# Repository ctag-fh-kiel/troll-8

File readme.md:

# CTAG TROLL8
TROLL8 is an Arduino Based μSynth development platform.
This repo contains:
  - [KiCad](http://kicad.org/) PCB design files ([schematics as pdf](https://github.com/ctag-fh-kiel/troll-8/blob/master/Docs/TROLL-8-Schematics.pdf))
	- You may order the PCB [here](http://dirtypcbs.com/store/designer/details/8229/2509/gerber-zip)
  - Silkscreen design files
  - Arduino examples
    - Midi controller (requires [hairless midi](http://projectgus.github.io/hairless-midiserial/))
	- Drum machine with Synth
    - ePiano (velocity sensitive)    
	- Step sequencer
    - Linear sequencer
    - Teensy 3.1 synthesizer
    - LED example
    - and more...
  - A short [presentation on TROLL8](https://github.com/ctag-fh-kiel/troll-8/blob/master/Docs/Talk_AmIEs2016_Manzke.pdf)
# Known Bugs
  - PCB design: Rotary knobs are not evenly spaced
# Authors / License
  - Authors are Robert Manzke (Main Author, FH-Kiel), Henrik Langer (FH-Kiel), Alexander Konradi (FH-Kiel)
  - Licensed under Creative Commons Attribution-NonCommercial-ShareAlike 4.0 International License
# Acknoledgements
  - All Arduino examples make use of the amazing [Mozzi Sound Library](http://sensorium.github.io/Mozzi/)
# Media

## [Gearnews English (click here)](https://www.gearnews.com/troll8-micro-sized-synthesizer-sequencer-controller-drum-machine/)

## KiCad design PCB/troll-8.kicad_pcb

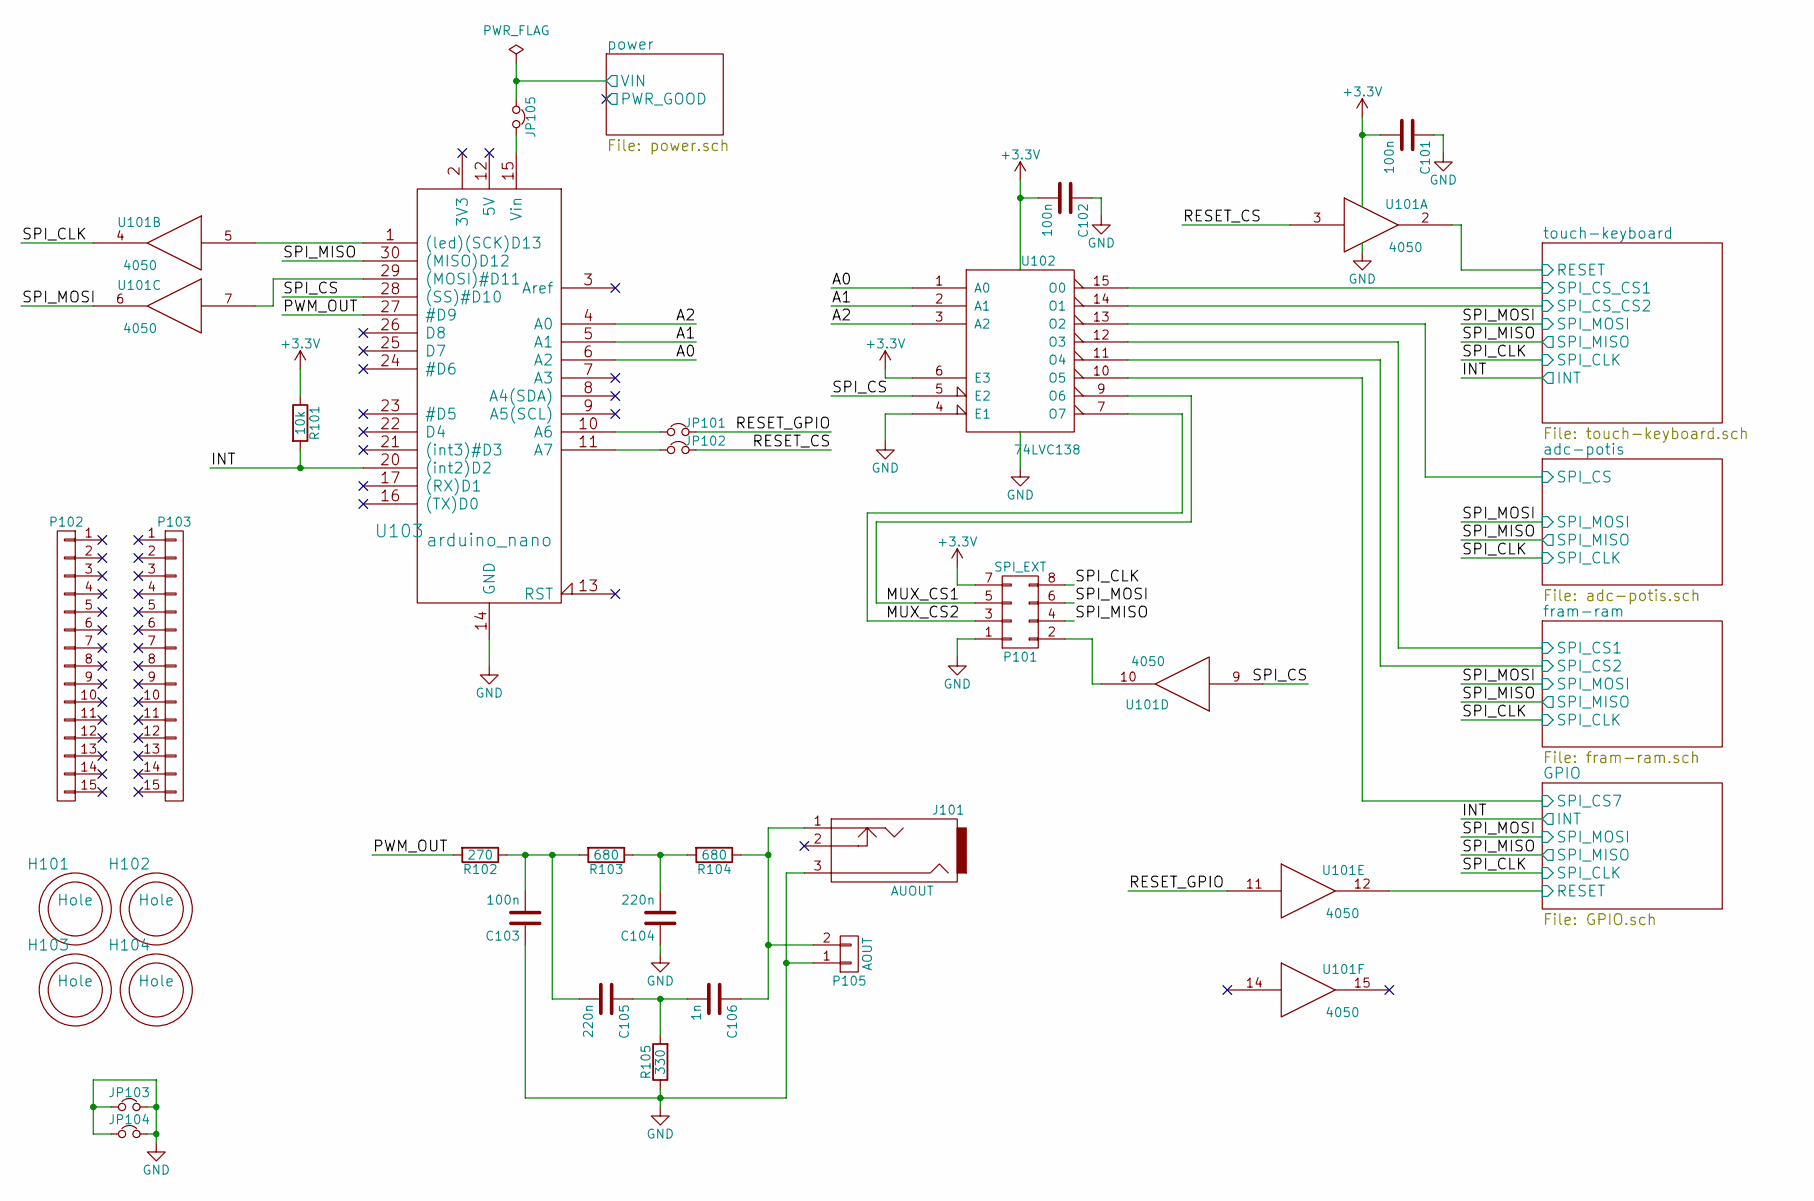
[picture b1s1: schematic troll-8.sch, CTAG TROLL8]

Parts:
C101, C102, C103: 100n; C_0603_HandSoldering
C104, C105: 220n; C_0603_HandSoldering
C106: 1n; C_0603_HandSoldering
H101, H102, H103, H104: Hole; Hole_3mm
J101: AUOUT; THONKICONN
JP101, JP102: Jumper_NC_Small; R_0603_HandSoldering
JP103, JP104: Jumper_NC_Small; R_0805_HandSoldering
JP105: Jumper_NC_Small; Pin_Header_Straight_1x02
P101: SPI_EXT; Pin_Header_Straight_2x04
P102, P103: Pin_Header_Straight_1x15
P105: AOUT; Pin_Header_Straight_1x02
R101: 10k; R_0603_HandSoldering
R102: 270; R_0603_HandSoldering
R103, R104: 680; R_0603_HandSoldering
R105: 330; R_0603_HandSoldering
U101: 4050; TSSOP-16_4.4x5mm_Pitch0.65mm
U102: 74LVC138; TSSOP-16_4.4x5mm_Pitch0.65mm
U103: arduino_nano; arduino_mini

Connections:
+3V3: C101.2, C102.2, P101.7, R101.1, U101.1 (VCC), U102.6 (E3), U102.16 (VCC); also elsewhere on the board
/A0: U102.1 (A0), U103.6 (A2)
/A1: U102.2 (A1), U103.5 (A1)
/A2: U102.3 (A2), U103.4 (A0)
/GPIO/RESET: U101.12; also elsewhere on the board
/GPIO/SPI_CS7: U102.10 (O5); also elsewhere on the board
/INT: R101.2, U103.20 ((int2)D2); also elsewhere on the board
/MUX_CS1: P101.5, U102.9 (O6)
/MUX_CS2: P101.3, U102.7 (O7)
/PWM_OUT: R102.2, U103.27 (#D9)
/RESET_CS: JP102.2, U101.3
/RESET_GPIO: JP101.2, U101.11
/SPI_CLK: P101.8, U101.4; also elsewhere on the board
/SPI_CS: U101.9, U102.5 (E2), U103.28 ((SS)#D10)
/SPI_MISO: P101.4, U103.30 ((MISO)D12); also elsewhere on the board
/SPI_MOSI: P101.6, U101.6; also elsewhere on the board
/adc-potis/SPI_CS: U102.13 (O2); also elsewhere on the board
/fram-ram/SPI_CS1: U102.12 (O3); also elsewhere on the board
/fram-ram/SPI_CS2: U102.11 (O4); also elsewhere on the board
/power/VIN: JP105.1; also elsewhere on the board
/touch-keyboard/RESET: U101.2; also elsewhere on the board
/touch-keyboard/SPI_CS_CS1: U102.15 (O0); also elsewhere on the board
/touch-keyboard/SPI_CS_CS2: U102.14 (O1); also elsewhere on the board
GND: C101.1, C102.1, C103.1, C104.1, J101.3, JP103.1, JP103.2, JP104.1, JP104.2, P101.1, P105.1, R105.1, U101.8 (VSS), U102.4 (E1), U102.8 (GND), U103.14 (GND), U103.19 (GND); also elsewhere on the board
unnamed: C103.2, C105.2, R102.1, R103.2
unnamed: C104.2, R103.1, R104.2
unnamed: C105.1, C106.2, R105.2
unnamed: C106.1, J101.1, P105.2, R104.1
unnamed: JP101.1, U103.10 (A6)
unnamed: JP102.1, U103.11 (A7)
unnamed: JP105.2, U103.15 (Vin)
unnamed: P101.2, U101.10
unnamed: U101.5, U103.1 ((led)(SCK)D13)
unnamed: U101.7, U103.29 ((MOSI)#D11)

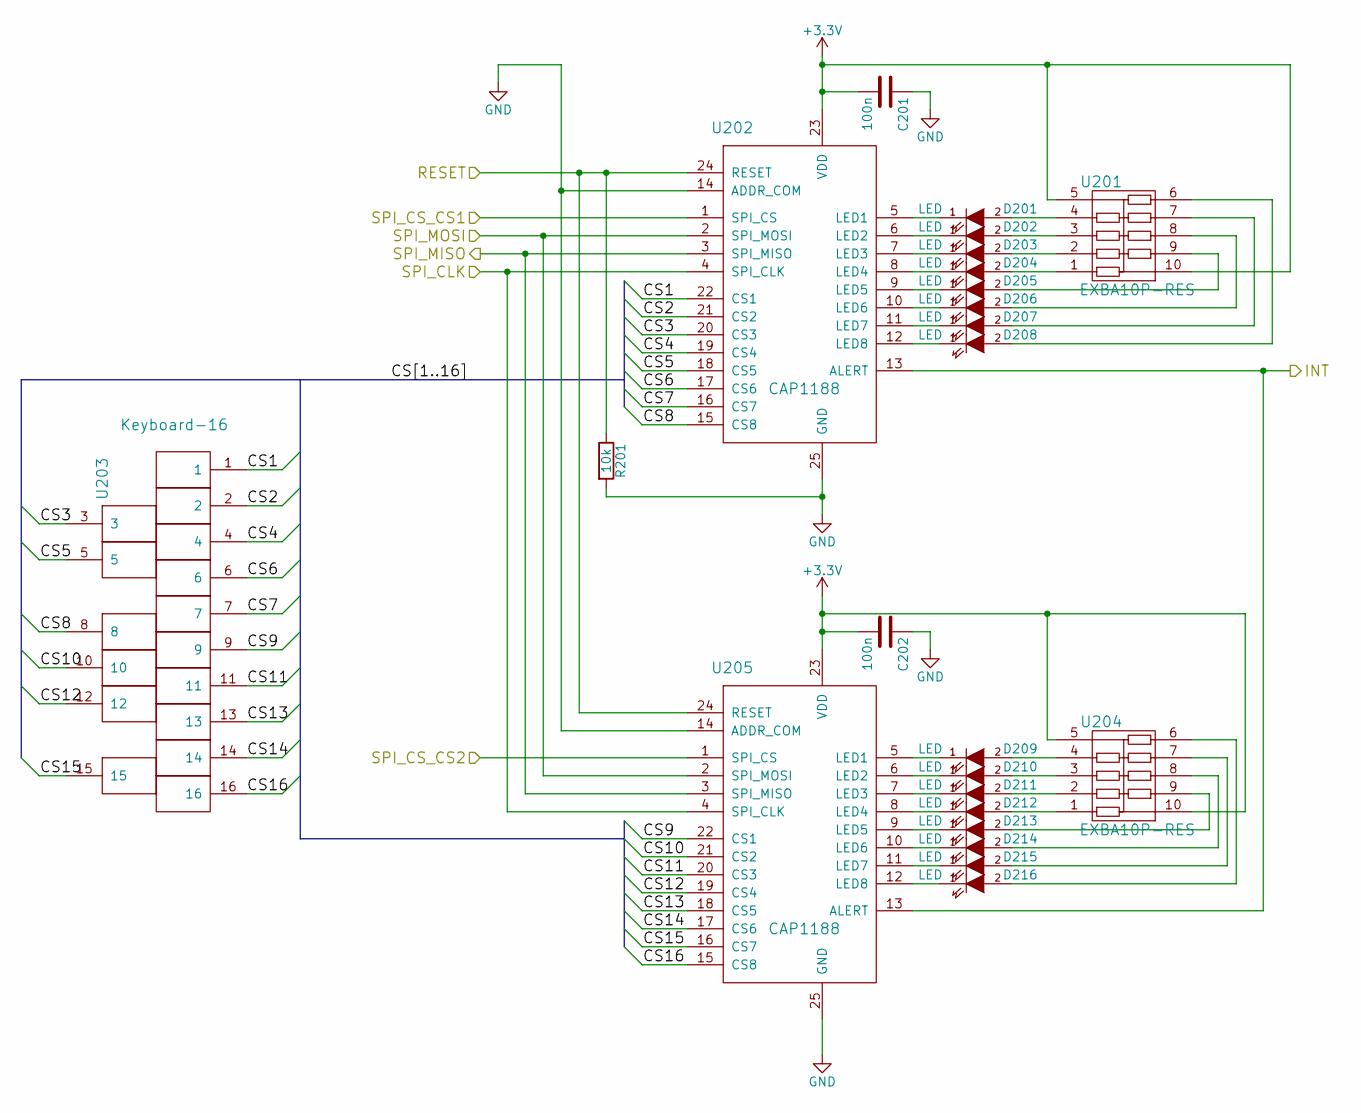
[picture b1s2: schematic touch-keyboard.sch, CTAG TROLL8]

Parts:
C201, C202: 100n; C_0603_HandSoldering
D201, D202, D203, D204, D205, D206, D207, D208, D209, D210, D211, D212, D213, D214, D215, D216: LED; LED-0603
R201: 10k; R_0603_HandSoldering
U201, U204: EXBA10P-RES; EXBA10P
U202, U205: CAP1188; QFN-24-1EP_4x4mm_Pitch0.5mm
U203: Keyboard-16; midi-keyboard-16

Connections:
+3V3: C201.2, C202.2, U201.5, U201.10, U202.23 (VDD), U204.5, U204.10, U205.23 (VDD); also elsewhere on the board
/INT: U202.13 (ALERT), U205.13 (ALERT); also elsewhere on the board
/SPI_CLK: U202.4 (SPI_CLK), U205.4 (SPI_CLK); also elsewhere on the board
/SPI_MISO: U202.3 (SPI_MISO), U205.3 (SPI_MISO); also elsewhere on the board
/SPI_MOSI: U202.2 (SPI_MOSI), U205.2 (SPI_MOSI); also elsewhere on the board
/touch-keyboard/CS1: U202.22 (CS1), U203.1
/touch-keyboard/CS2: U202.21 (CS2), U203.2
/touch-keyboard/CS3: U202.20 (CS3), U203.3
/touch-keyboard/CS4: U202.19 (CS4), U203.4
/touch-keyboard/CS5: U202.18 (CS5), U203.5
/touch-keyboard/CS6: U202.17 (CS6), U203.6
/touch-keyboard/CS7: U202.16 (CS7), U203.7
/touch-keyboard/CS8: U202.15 (CS8), U203.8
/touch-keyboard/CS9: U203.9, U205.22 (CS1)
/touch-keyboard/CS10: U203.10, U205.21 (CS2)
/touch-keyboard/CS11: U203.11, U205.20 (CS3)
/touch-keyboard/CS12: U203.12, U205.19 (CS4)
/touch-keyboard/CS13: U203.13, U205.18 (CS5)
/touch-keyboard/CS14: U203.14, U205.17 (CS6)
/touch-keyboard/CS15: U203.15, U205.16 (CS7)
/touch-keyboard/CS16: U203.16, U205.15 (CS8)
/touch-keyboard/RESET: R201.1, U202.24 (RESET), U205.24 (RESET); also elsewhere on the board
/touch-keyboard/SPI_CS_CS1: U202.1 (SPI_CS); also elsewhere on the board
/touch-keyboard/SPI_CS_CS2: U205.1 (SPI_CS); also elsewhere on the board
GND: C201.1, C202.1, R201.2, U202.14 (ADDR_COM), U202.25 (GND), U205.14 (ADDR_COM), U205.25 (GND); also elsewhere on the board
unnamed: D201.1 (K), U202.5 (LED1)
unnamed: D201.2 (A), U201.4
unnamed: D202.1 (K), U202.6 (LED2)
unnamed: D202.2 (A), U201.3
unnamed: D203.1 (K), U202.7 (LED3)
unnamed: D203.2 (A), U201.2
unnamed: D204.1 (K), U202.8 (LED4)
unnamed: D204.2 (A), U201.1
unnamed: D205.1 (K), U202.9 (LED5)
unnamed: D205.2 (A), U201.9
unnamed: D206.1 (K), U202.10 (LED6)
unnamed: D206.2 (A), U201.8
unnamed: D207.1 (K), U202.11 (LED7)
unnamed: D207.2 (A), U201.7
unnamed: D208.1 (K), U202.12 (LED8)
unnamed: D208.2 (A), U201.6
unnamed: D209.1 (K), U205.5 (LED1)
unnamed: D209.2 (A), U204.4
unnamed: D210.1 (K), U205.6 (LED2)
unnamed: D210.2 (A), U204.3
unnamed: D211.1 (K), U205.7 (LED3)
unnamed: D211.2 (A), U204.2
unnamed: D212.1 (K), U205.8 (LED4)
unnamed: D212.2 (A), U204.1
unnamed: D213.1 (K), U205.9 (LED5)
unnamed: D213.2 (A), U204.9
unnamed: D214.1 (K), U205.10 (LED6)
unnamed: D214.2 (A), U204.8
unnamed: D215.1 (K), U205.11 (LED7)
unnamed: D215.2 (A), U204.7
unnamed: D216.1 (K), U205.12 (LED8)
unnamed: D216.2 (A), U204.6

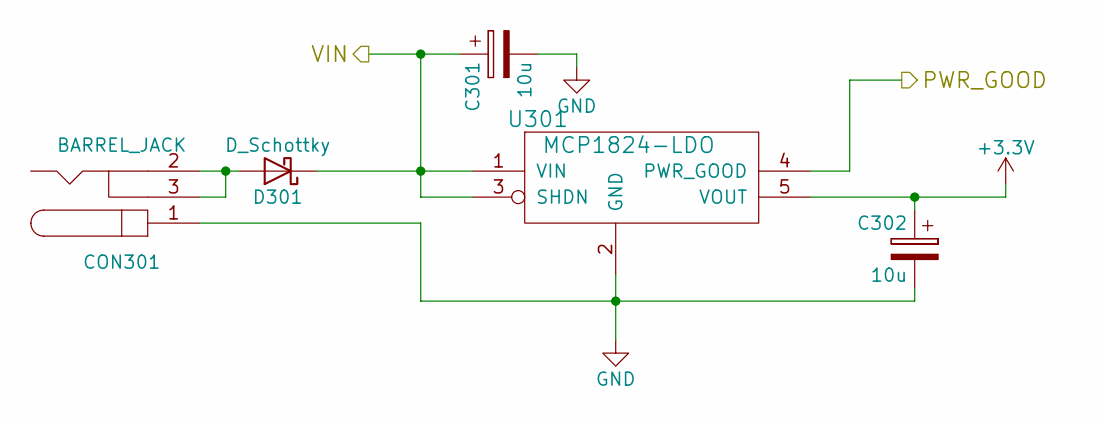
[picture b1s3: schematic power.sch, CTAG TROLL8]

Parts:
C301, C302: 10u; c_elec_4x5.7
CON301: BARREL_JACK; BARELL_CLIFF_DC10L
D301: D_Schottky; SOD-123
U301: MCP1824-LDO; SOT-23-5

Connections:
+3V3: C302.1, U301.5 (VOUT); also elsewhere on the board
/power/PWR_GOOD: U301.4 (PWR_GOOD)
/power/VIN: C301.1, D301.1 (K), U301.1 (VIN), U301.3 (SHDN); also elsewhere on the board
GND: C301.2, C302.2, CON301.1, U301.2 (GND); also elsewhere on the board
unnamed: CON301.2, CON301.3, D301.2 (A)

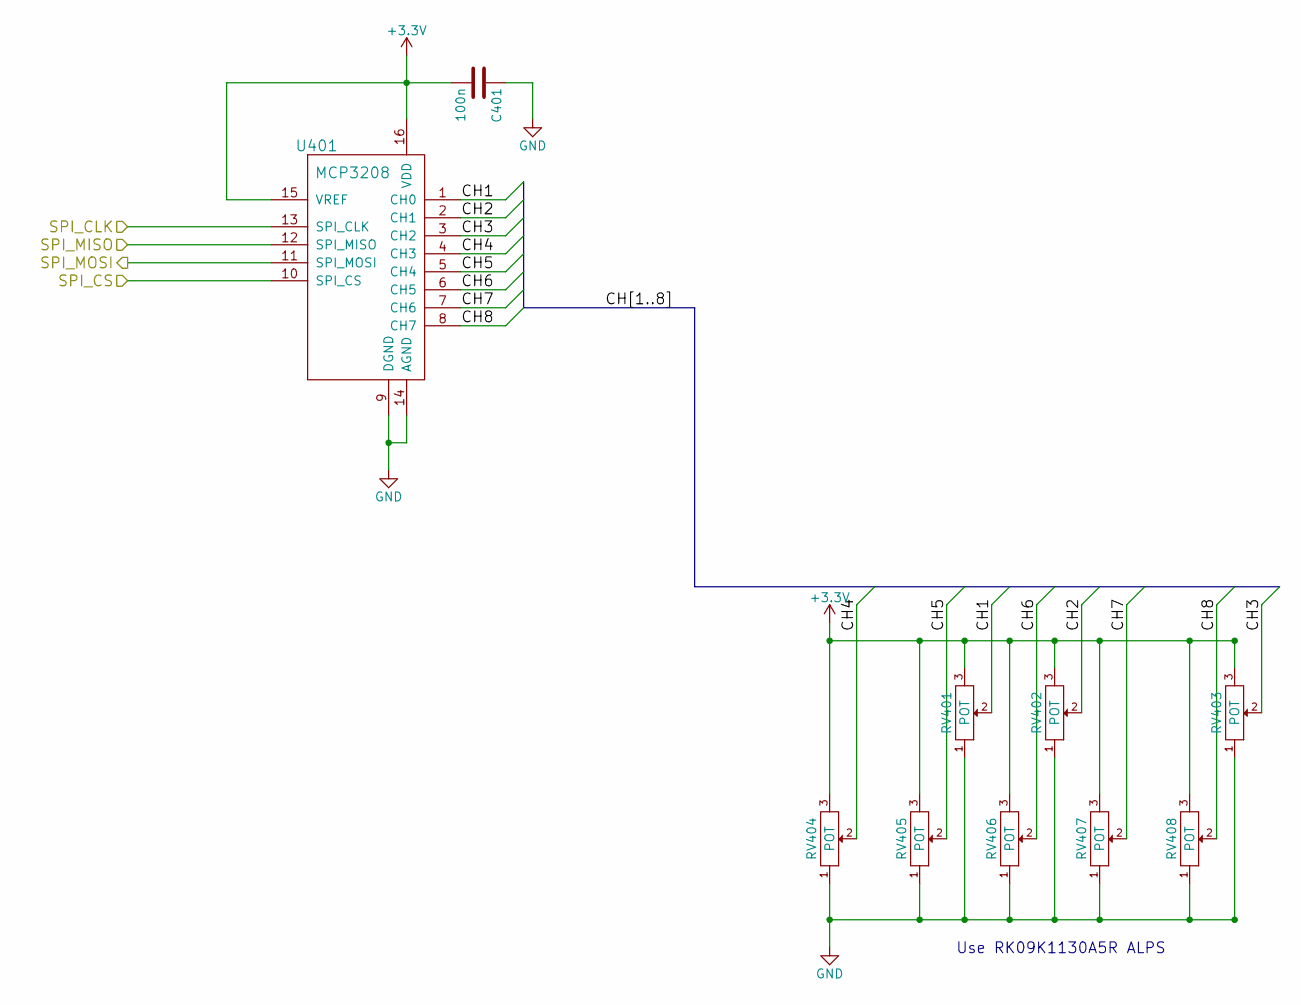
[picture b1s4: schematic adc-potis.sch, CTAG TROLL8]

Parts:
C401: 100n; C_0603_HandSoldering
RV401, RV402, RV403, RV404, RV405, RV406, RV407, RV408: POT; Alps-RK09
U401: MCP3208; SOIC-16_3.9x9.9mm_Pitch1.27mm

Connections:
+3V3: C401.2, RV401.3, RV402.3, RV403.3, RV404.3, RV405.3, RV406.3, RV407.3, RV408.3, U401.15 (VREF), U401.16 (VDD); also elsewhere on the board
/SPI_CLK: U401.13 (SPI_CLK); also elsewhere on the board
/SPI_MISO: U401.12 (SPI_MISO); also elsewhere on the board
/SPI_MOSI: U401.11 (SPI_MOSI); also elsewhere on the board
/adc-potis/CH1: RV401.2, U401.1 (CH0)
/adc-potis/CH2: RV402.2, U401.2 (CH1)
/adc-potis/CH3: RV403.2, U401.3 (CH2)
/adc-potis/CH4: RV404.2, U401.4 (CH3)
/adc-potis/CH5: RV405.2, U401.5 (CH4)
/adc-potis/CH6: RV406.2, U401.6 (CH5)
/adc-potis/CH7: RV407.2, U401.7 (CH6)
/adc-potis/CH8: RV408.2, U401.8 (CH7)
/adc-potis/SPI_CS: U401.10 (SPI_CS); also elsewhere on the board
GND: C401.1, RV401.1, RV402.1, RV403.1, RV404.1, RV405.1, RV406.1, RV407.1, RV408.1, U401.9 (DGND), U401.14 (AGND); also elsewhere on the board

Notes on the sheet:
Use RK09K1130A5R ALPS

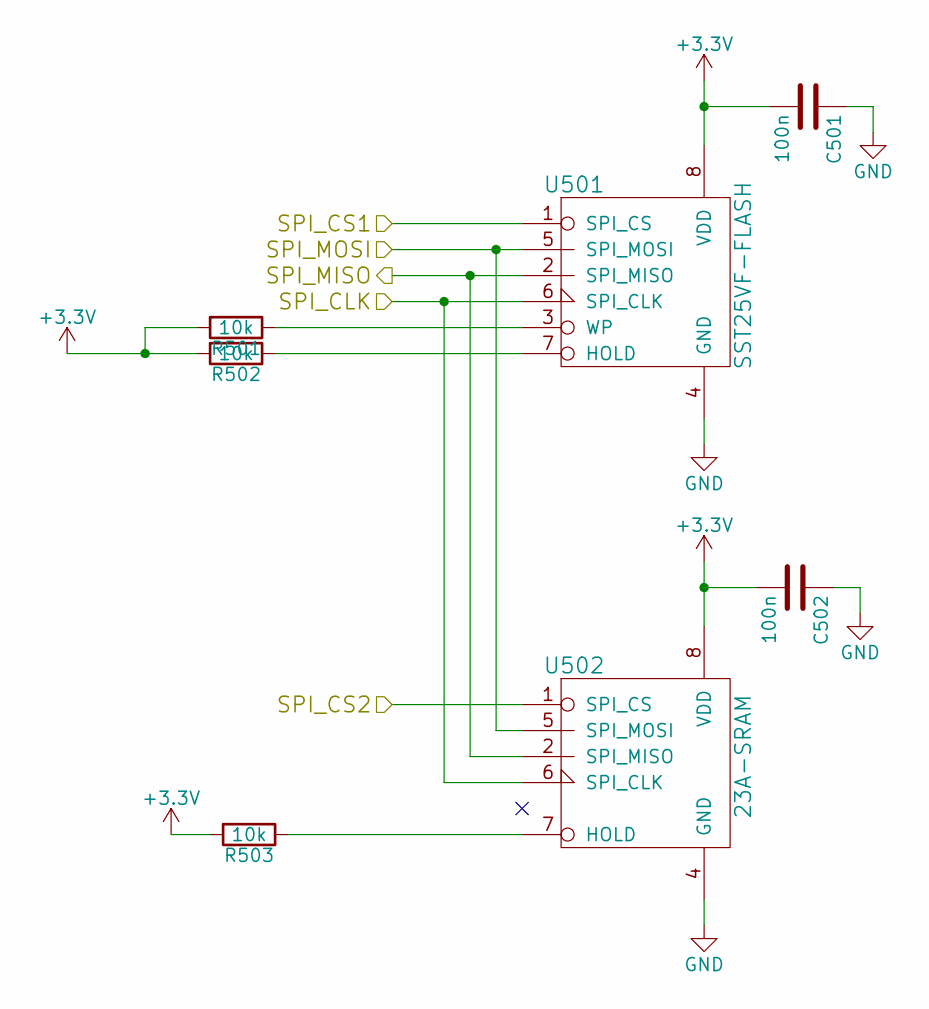
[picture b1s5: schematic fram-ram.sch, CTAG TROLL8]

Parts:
C501, C502: 100n; C_0603_HandSoldering
R501, R502, R503: 10k; R_0603_HandSoldering
U501: SST25VF-FLASH; SOIC-8_3.9x4.9mm_Pitch1.27mm
U502: 23A-SRAM; SOIC-8_3.9x4.9mm_Pitch1.27mm

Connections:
+3V3: C501.2, C502.2, R501.2, R502.2, R503.2, U501.8 (VDD), U502.8 (VDD); also elsewhere on the board
/SPI_CLK: U501.6 (SPI_CLK), U502.6 (SPI_CLK); also elsewhere on the board
/SPI_MISO: U501.2 (SPI_MISO), U502.2 (SPI_MISO); also elsewhere on the board
/SPI_MOSI: U501.5 (SPI_MOSI), U502.5 (SPI_MOSI); also elsewhere on the board
/fram-ram/SPI_CS1: U501.1 (SPI_CS); also elsewhere on the board
/fram-ram/SPI_CS2: U502.1 (SPI_CS); also elsewhere on the board
GND: C501.1, C502.1, U501.4 (GND), U502.4 (GND); also elsewhere on the board
unnamed: R501.1, U501.3 (WP)
unnamed: R502.1, U501.7 (HOLD)
unnamed: R503.1, U502.7 (HOLD)

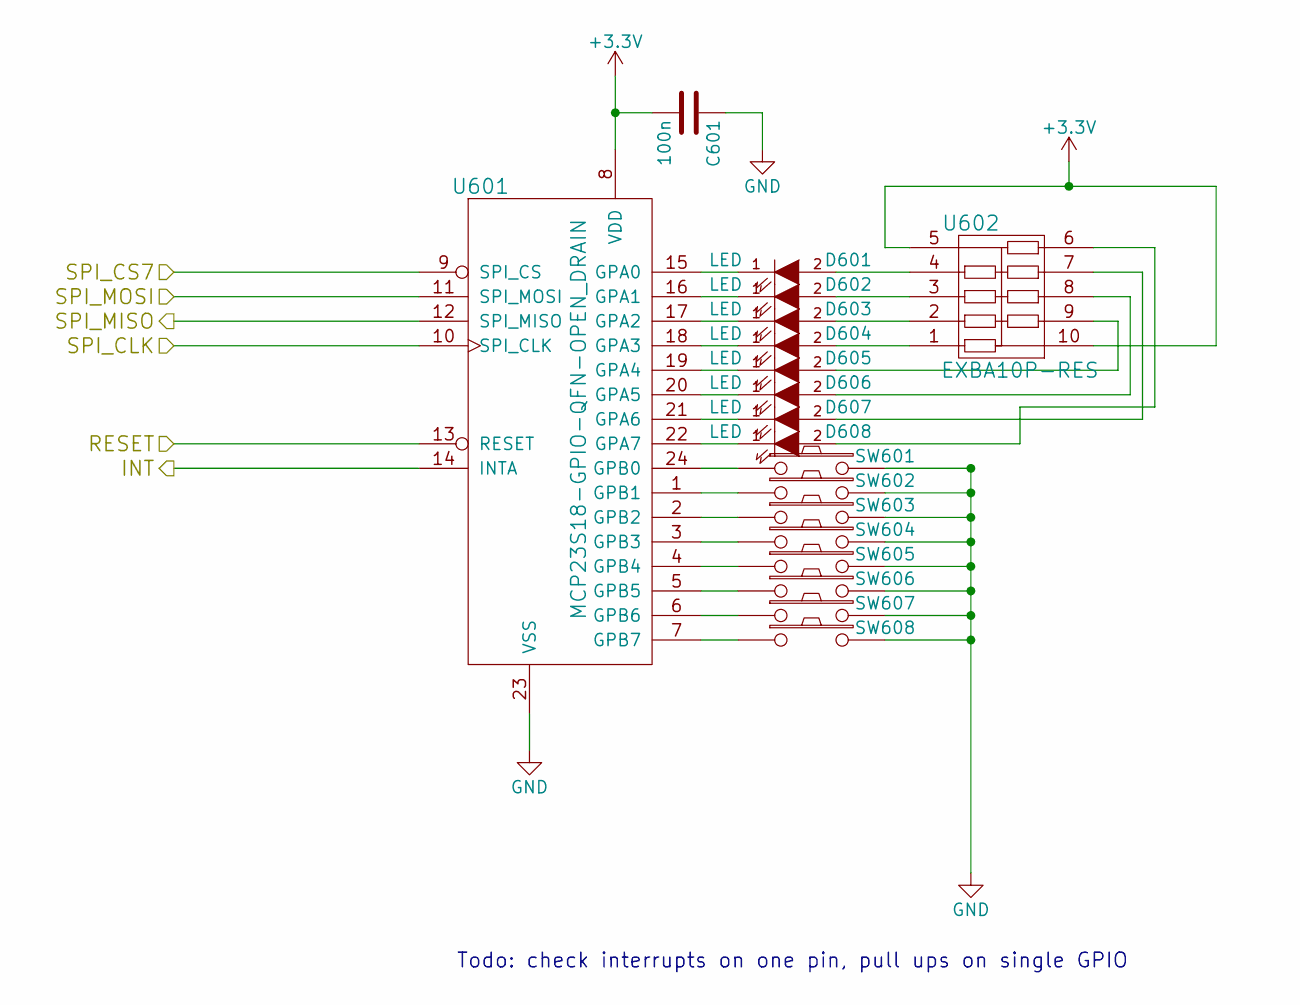
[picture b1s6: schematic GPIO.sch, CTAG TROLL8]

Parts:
C601: 100n; C_0603_HandSoldering
D601, D602, D603, D604, D605, D606, D607, D608: LED; LED-0603
SW601, SW602, SW603, SW604, SW605, SW606, SW607, SW608: SW_PUSH; TE-147873-1-Pushbutton
U601: MCP23S18-GPIO-QFN-OPEN_DRAIN; QFN-24-1EP_4x4mm_Pitch0.5mm
U602: EXBA10P-RES; EXBA10P

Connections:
+3V3: C601.2, U601.8 (VDD), U602.5, U602.10; also elsewhere on the board
/GPIO/RESET: U601.13 (RESET); also elsewhere on the board
/GPIO/SPI_CS7: U601.9 (SPI_CS); also elsewhere on the board
/INT: U601.14 (INTA); also elsewhere on the board
/SPI_CLK: U601.10 (SPI_CLK); also elsewhere on the board
/SPI_MISO: U601.12 (SPI_MISO); also elsewhere on the board
/SPI_MOSI: U601.11 (SPI_MOSI); also elsewhere on the board
GND: C601.1, SW601.2, SW602.2, SW603.2, SW604.2, SW605.2, SW606.2, SW607.2, SW608.2, U601.23 (VSS); also elsewhere on the board
unnamed: D601.1 (K), U601.15 (GPA0)
unnamed: D601.2 (A), U602.4
unnamed: D602.1 (K), U601.16 (GPA1)
unnamed: D602.2 (A), U602.3
unnamed: D603.1 (K), U601.17 (GPA2)
unnamed: D603.2 (A), U602.2
unnamed: D604.1 (K), U601.18 (GPA3)
unnamed: D604.2 (A), U602.1
unnamed: D605.1 (K), U601.19 (GPA4)
unnamed: D605.2 (A), U602.9
unnamed: D606.1 (K), U601.20 (GPA5)
unnamed: D606.2 (A), U602.8
unnamed: D607.1 (K), U601.21 (GPA6)
unnamed: D607.2 (A), U602.7
unnamed: D608.1 (K), U601.22 (GPA7)
unnamed: D608.2 (A), U602.6
unnamed: SW601.1, U601.24 (GPB0)
unnamed: SW602.1, U601.1 (GPB1)
unnamed: SW603.1, U601.2 (GPB2)
unnamed: SW604.1, U601.3 (GPB3)
unnamed: SW605.1, U601.4 (GPB4)
unnamed: SW606.1, U601.5 (GPB5)
unnamed: SW607.1, U601.6 (GPB6)
unnamed: SW608.1, U601.7 (GPB7)

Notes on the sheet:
Todo: check interrupts on one pin, pull ups on single GPIO

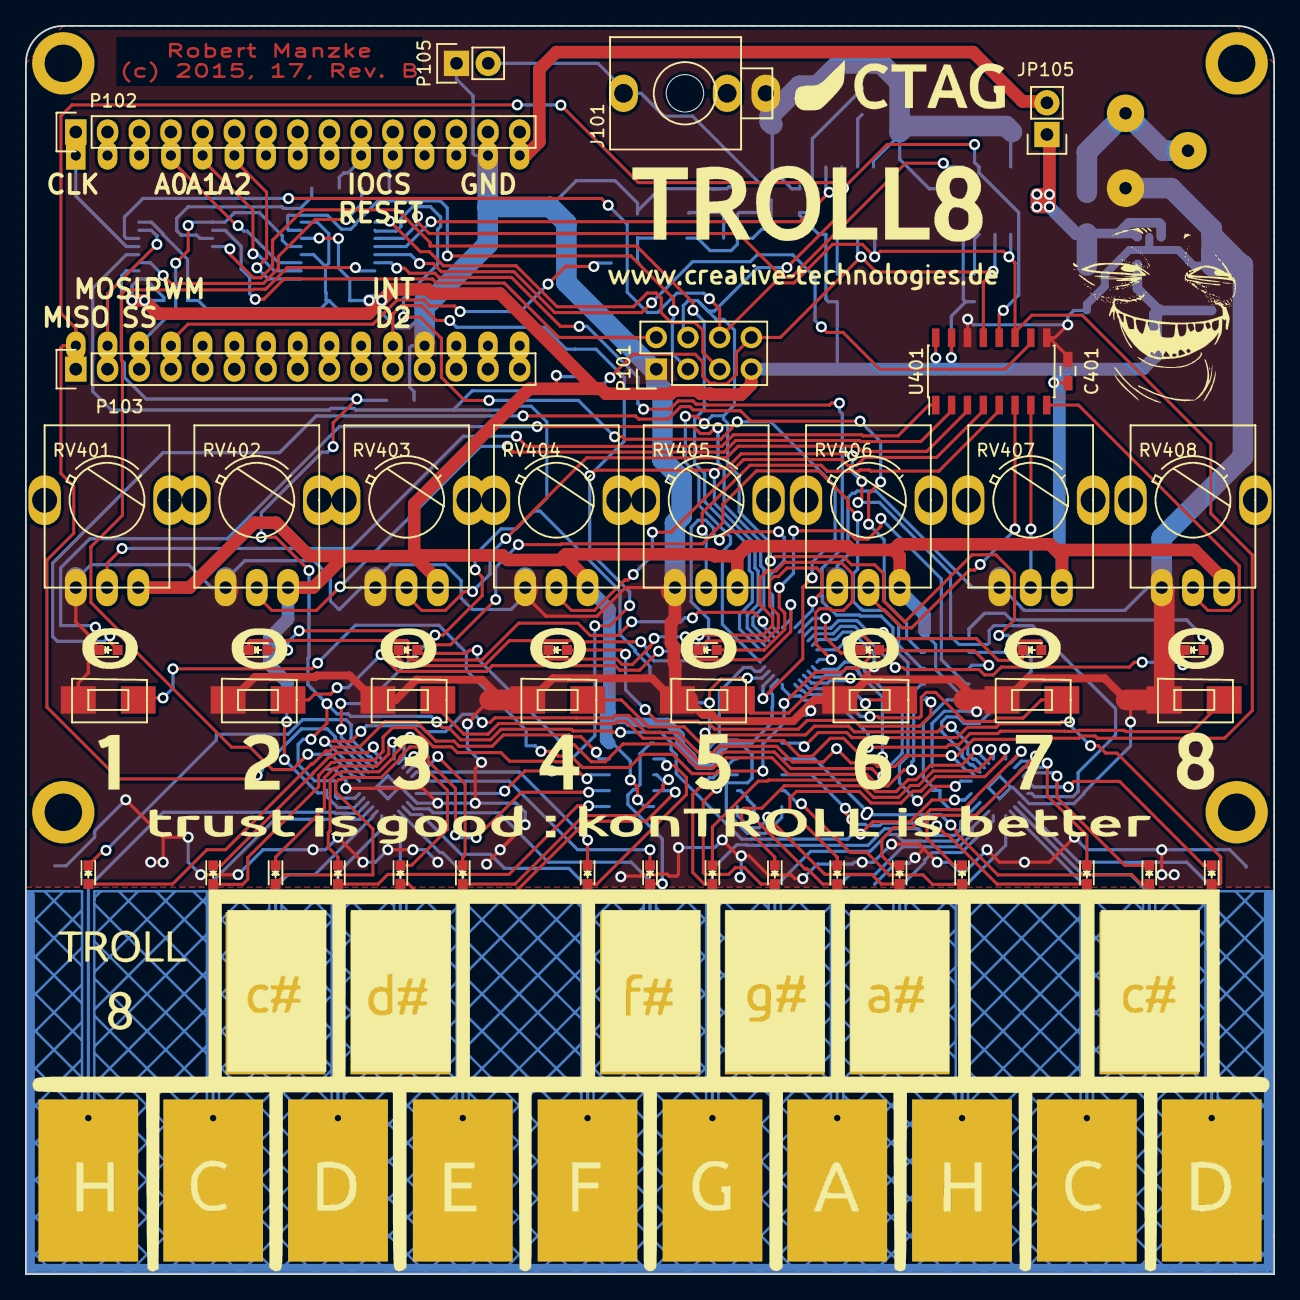
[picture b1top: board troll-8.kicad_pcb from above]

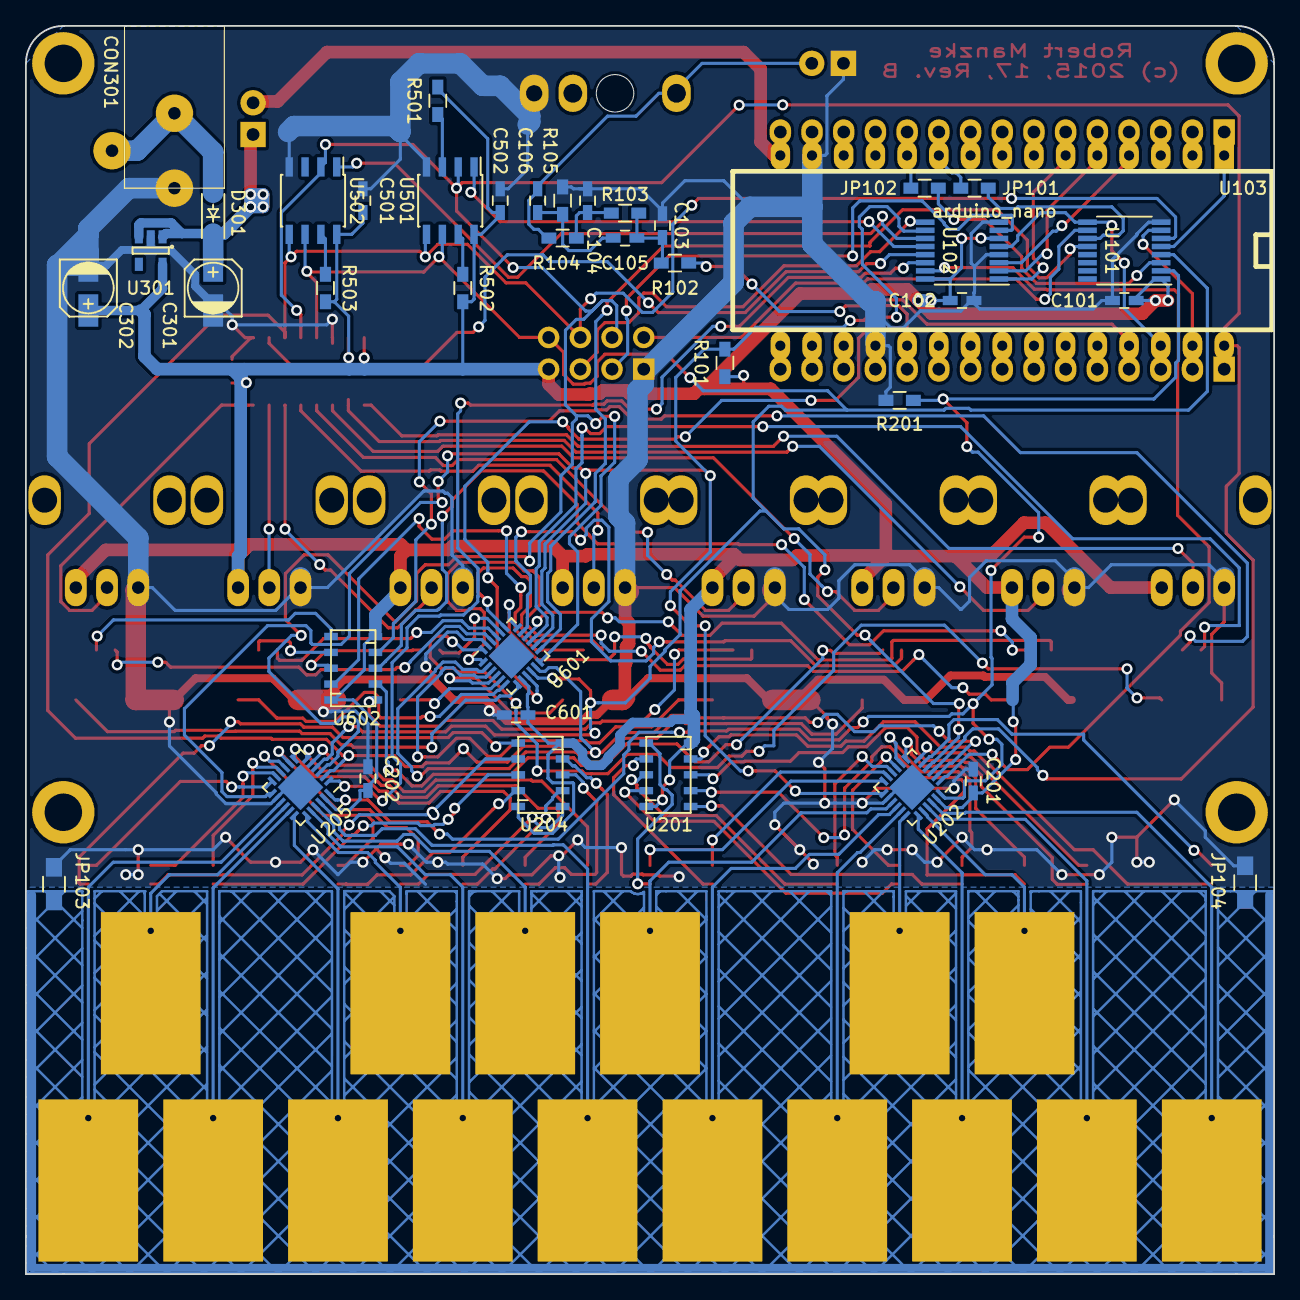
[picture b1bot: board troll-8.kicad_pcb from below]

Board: 2 copper layers, 100.0 x 100.0 mm, 93 parts (40 on the bottom side), 118 nets.

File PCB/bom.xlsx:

Mouser | Id | Designator | Package | Quantity | Designation | Manuf ID |  | Notes
x | 1 | C103,C102,C101,C201,C202,C401,C502,C501,C601 | C_0603_HandSoldering | 9 | 100n | C0603C104K5RACTU
x | 2 | C104, C105 | C_0603_HandSoldering | 2 | 220n | 02016D224KAT2A
x | 3 | C106 | C_0603_HandSoldering | 1 | 1n | GCM188R71H102KA37D
x | 4 | C301,C302 | c_elec_4x5.7 | 2 | 10u | EEE-FC1C100R
x | 5 | CON301 | BARELL_CLIFF_DC10L | 1 | BARREL_JACK | PJ-102B
x | 6 | D201,D202,D203,D204,D205,D206,D207,D208,D209,D210,D211,D212,D213,D214,D215,D216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 | LED-0603 | 24 | LED | 696-SMLLXFP0603SICTR
x | 7 | D301 | SOD-123 | 1 | D_Schottky | STPS140Z
x | 8 | JP101,JP102 | R_0603_HandSoldering | 2 | Jumper_NC_Small | ERJ-3GEY0R00V
Thonk | 9 | J101 | Thonkicon | 1 | AUOUT | PJ301M-12 |  | https://www.thonk.co.uk/shop/3-5mm-jacks/
x | 10 | R102 | R_0603_HandSoldering | 1 | 270 | ERJ3EKF2700V
x | 11 | R103,R104 | R_0603_HandSoldering | 2 | 680 | ERJ3EKF6800V
x | 12 | R105 | R_0603_HandSoldering | 1 | 330 | ERJ3EKF3300V
x | 13 | R201,R501,R502,R503,R101 | R_0603_HandSoldering | 5 | 10k | ERJ3EKF1002V
x | 14 | SW601,SW602,SW603,SW604,SW605,SW606,SW607,SW608 | TE-147873-1-Pushbutton | 8 | SW_PUSH | 147873-1
x | 15 | U102 | TSSOP-16_4.4x5mm_Pitch0.65mm | 1 | 74LVC138 | SN74LVC138APWR
x | 16 | U301 | SOT-23-5 | 1 | MCP1755 | MCP1755T-3302E/OT
x | 17 | U401 | SOIC-16_3.9x9.9mm_Pitch1.27mm | 1 | MCP3208 | MCP3008-I/SL |  | Using 10 bit for now
x | 18 | U501 | SOIC-8_3.9x4.9mm_Pitch1.27mm | 1 | SST25VF-FLASH | SST25VF080B-80-4I-SAE
x | 19 | U502 | SOIC-8_3.9x4.9mm_Pitch1.27mm | 1 | 23LC1024-I/SN | 23LC1024-I/SN
x | 20 | U101 | TSSOP-16_4.4x5mm_Pitch0.65mm | 1 | 4050 | CD74HC4050PWR
x | 21 | U201,U204,U602 | EXBA10P | 3 | EXBA10P-RES | EXB-A10P471J |  | EXB-A10P331J auch kaufen
x | 22 | P101 | Pin_Header_Straight_2x04 | 1 | SPI_EXT | M20-7830446
x | 23 | P102,P103 | Pin_Header_Straight_1x15 | 2 | ~ | M20-7821546
x | 24 | U202,U205 | QFN-24-1EP_4x4mm_Pitch0.5mm | 2 | CAP1188 | CAP1188-1-CP-TR
x | 25 | U601 | QFN-24-1EP_4x4mm_Pitch0.5mm | 1 | MCP23S18-GPIO-QFN-OPEN_DRAIN | MCP23S18-E/MJ
x | 26 | JP103,JP104 | R_0805_HandSoldering | 2 | Jumper_NC_Small | RC0805JR-070RL
x | 27 | RV401,RV402,RV403,RV404,RV405,RV406,RV407,RV408 | Alps-RK09 | 8 | POT | RK09K1130081 |  | With center dip
x

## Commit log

2017-04-15 initial
2017-04-15 .md fixed
2017-04-16 added pdf of schematics
2017-04-16 added direct documenation links
2017-04-16 more links
2017-06-01 changed readme
2017-11-28 redesign, logo and audio connector changed
2017-11-28 small changes silk screen
2021-11-08 Update readme.md
    https://forum.kicad.info/t/warning-avoid-all-links-to-kicad-pcb-org-use-kicad-org/31521

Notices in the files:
PCB/GPIO.sch:
Licensed under a Creative Commons Attribution-NonCommercial-ShareAlike 4.0
PCB/troll-8.kicad_pcb:
(c) 2015, 17, Rev. B
